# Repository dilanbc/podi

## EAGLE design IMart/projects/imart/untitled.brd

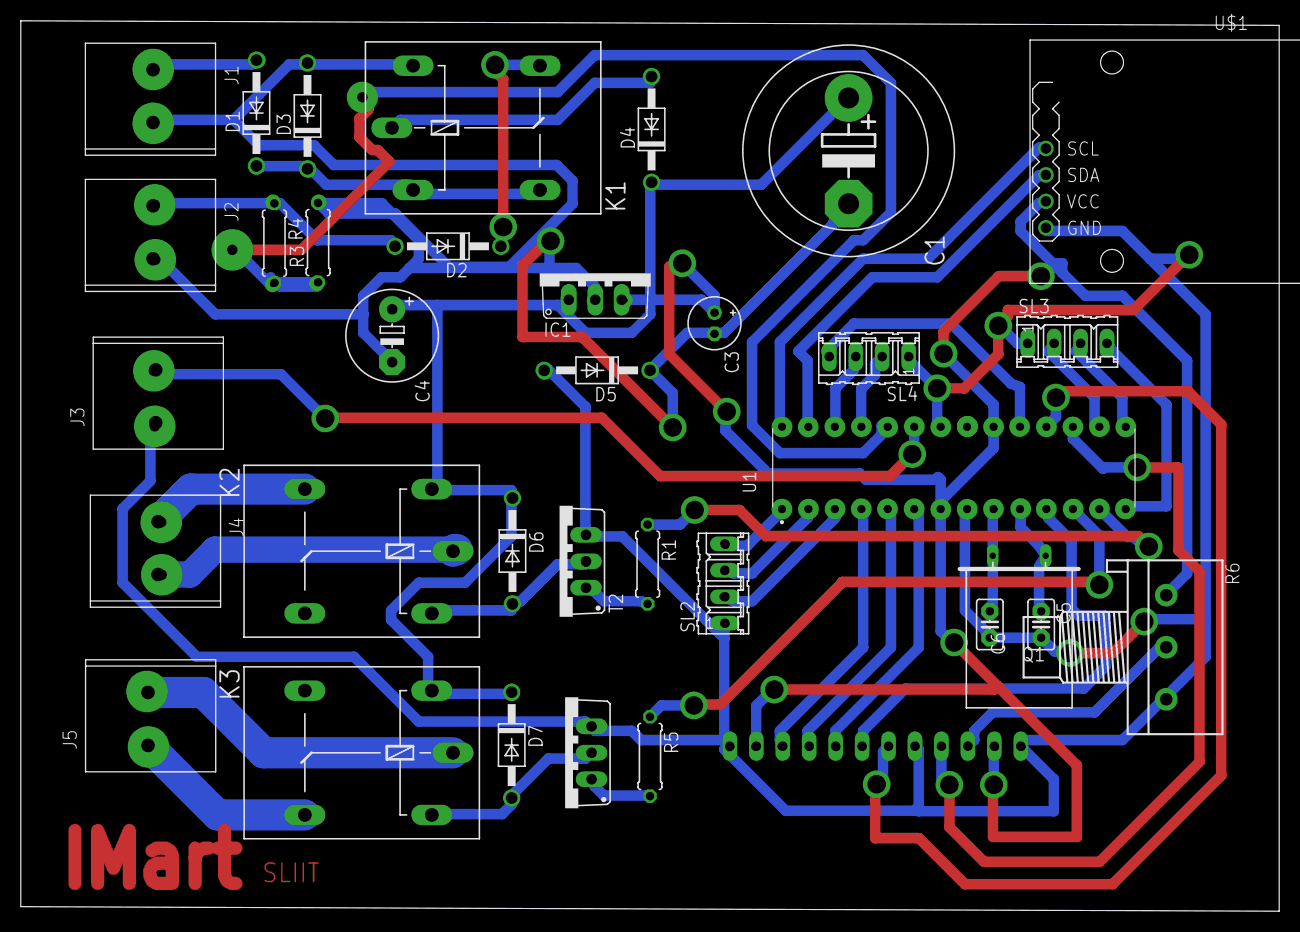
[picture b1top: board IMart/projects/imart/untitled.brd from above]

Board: 2 copper layers, 120.9 x 85.5 mm, 35 parts (1 on the bottom side), 41 nets.

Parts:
C1: EB20D
C3: E2-5
C4: E5-8,5
C5, C6: C025-025X050
D1, D2, D3, D4, D5, D6, D7: 1N4004; DO41-10
IC1: 788TV; TO220V
J1, J2, J3, J4, J5: 691201520002
K1, K2, K3: G5L; G5LE
Q1: Q
R1, R3, R4, R5: 0207/7
R6: 3RP/1610N
SL1: 12P
SL2, SL3, SL4: 04P
T1, T2: 2SC1306; TO220BV
U1: ATMEGA328P-PU; DIP-28
U$1: RTC-DS3231-AT24C32

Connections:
unnamed: D1.A, J1.1
unnamed: D2.A, J2.1, R4.1
unnamed: C1.-, C3.-, C4.-, D3.A, D5.C, IC1.2, J1.2, J2.2, K1.2, R3.2
unnamed: D2.C, K1.O
unnamed: D1.C, D3.C, K1.1, K1.S
unnamed: D4.A, K1.P
unnamed: R5.1, U1.12
unnamed: C3.+, IC1.3, R6.1, SL1.2, SL1.11, U1.7, U1.20, U$1.J1.5
unnamed: C5.2, C6.2, D5.A, J3.1, R6.3, SL1.1, SL1.5, SL1.12, SL2.1, SL3.1, SL4.1, T1.3, T2.3, U1.8, U1.22, U$1.J1.6
unnamed: C6.1, Q1.2, U1.9
unnamed: C5.1, Q1.1, U1.10
unnamed: U1.28, U$1.J1.3
unnamed: U1.27, U$1.J1.4
unnamed: SL1.7, U1.11
unnamed: R6.2, SL1.3
unnamed: SL1.4, U1.17
unnamed: SL1.6, U1.18
unnamed: SL1.8, U1.6
unnamed: SL1.9, U1.5
unnamed: SL1.10, U1.4
unnamed: J3.2, U1.23
unnamed: J4.2, K2.P
unnamed: J4.1, K2.S
unnamed: R3.1, R4.2, U1.24
unnamed: R1.1, U1.13
unnamed: R1.2, T2.1
unnamed: J5.2, K3.P
unnamed: D6.A, K2.2, T2.2
unnamed: J5.1, K3.O
unnamed: C1.+, C4.+, D4.C, D6.C, D7.C, IC1.1, K2.1, K3.1
unnamed: R5.2, T1.1
unnamed: D7.A, K3.2, T1.2
unnamed: SL2.4, U1.1
unnamed: SL2.3, U1.2
unnamed: SL2.2, U1.3
unnamed: SL3.4, U1.14
unnamed: SL3.3, U1.15
unnamed: SL3.2, U1.16
unnamed: SL4.2, U1.25
unnamed: SL4.3, U1.26
unnamed: SL4.4, U1.19

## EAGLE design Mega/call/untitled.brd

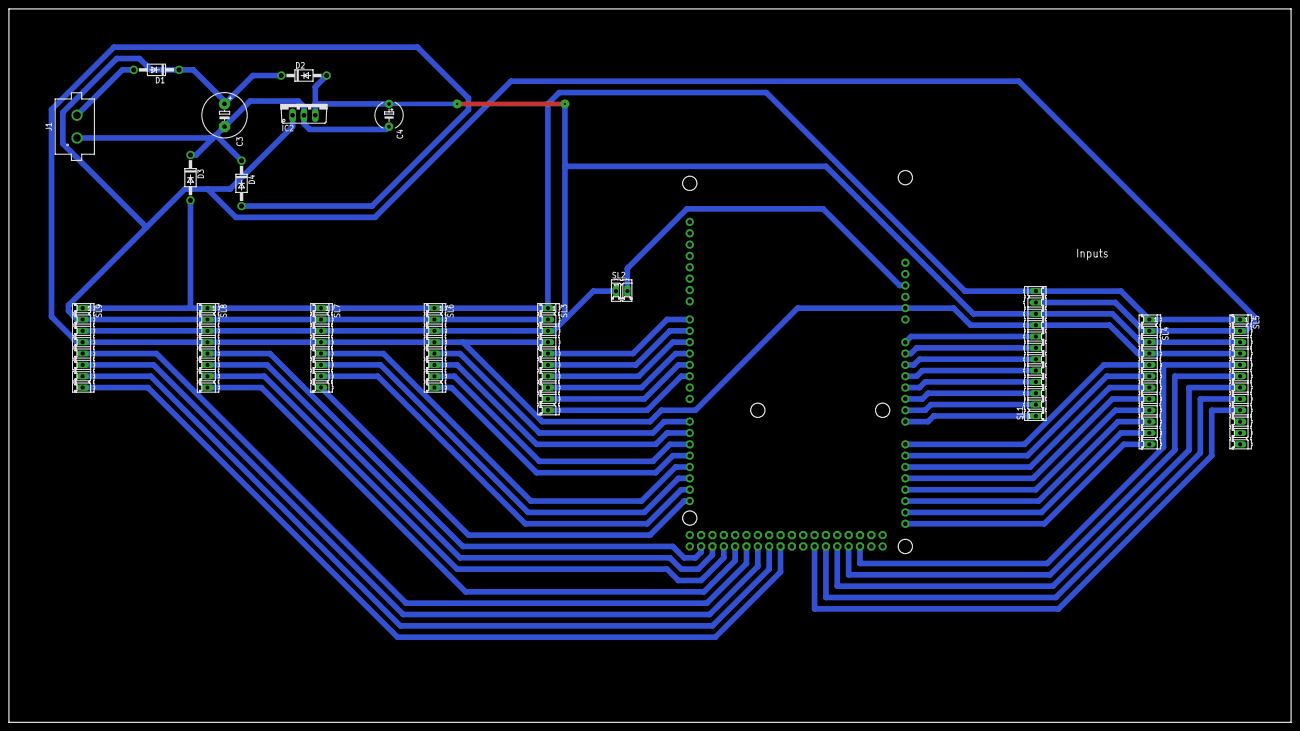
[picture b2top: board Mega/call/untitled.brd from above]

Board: 2 copper layers, 287.0 x 159.7 mm, 18 parts (1 on the bottom side), 50 nets.

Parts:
B1: ARDUINO_MEGA_R3FULL; ARDUINO_MEGA
C3: E5-10,5
C4: E5-6
D1, D2, D3, D4: 1N4004; DO41-10
IC2: 786TV; TO220V
J1: 691305530002
SL1, SL4, SL5: 12P
SL2: 02P
SL3: 10P
SL6, SL7, SL8, SL9: 08P

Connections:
GND: B1.GND@1, D4.A, SL1.9, SL3.4, SL4.4, SL5.4, SL6.4, SL7.4, SL8.4, SL9.4
unnamed: B1.A7, SL1.1
unnamed: B1.A6, SL1.2
unnamed: B1.A5, SL1.3
unnamed: B1.A4, SL1.4
unnamed: B1.A3, SL1.5
unnamed: B1.A2, SL1.6
unnamed: B1.A1, SL1.7
unnamed: B1.A0, SL1.8
unnamed: D3.A, SL1.12, SL3.1, SL4.1, SL5.1, SL6.1, SL7.1, SL8.1, SL9.1
unnamed: D1.A, J1.2
unnamed: C3.+, D1.C, D2.C, IC2.1, SL1.11, SL3.2, SL4.2, SL5.2, SL6.2, SL7.2, SL8.2, SL9.2
unnamed: C4.+, D2.A, IC2.3, SL1.10, SL2.1, SL3.3, SL4.3, SL5.3, SL6.3, SL7.3, SL8.3, SL9.3
unnamed: B1.2, SL3.10
unnamed: C3.-, C4.-, D3.C, D4.C, IC2.2, J1.1
unnamed: B1.3, SL3.9
unnamed: B1.5V@0, SL2.2
unnamed: B1.4, SL3.8
unnamed: B1.5, SL3.7
unnamed: B1.6, SL3.6
unnamed: B1.7, SL3.5
unnamed: B1.A8, SL4.5
unnamed: B1.A9, SL4.6
unnamed: B1.A10, SL4.7
unnamed: B1.A11, SL4.8
unnamed: B1.A12, SL4.9
unnamed: B1.A13, SL4.10
unnamed: B1.A14, SL4.11
unnamed: B1.A15, SL4.12
unnamed: B1.18, SL7.5
unnamed: B1.14, SL6.5
unnamed: B1.51, SL5.5
unnamed: B1.49, SL5.6
unnamed: B1.47, SL5.7
unnamed: B1.45, SL5.8
unnamed: B1.43, SL5.9
unnamed: B1.21, SL7.8
unnamed: B1.15, SL6.6
unnamed: B1.17, SL6.8
unnamed: B1.20, SL7.7
unnamed: B1.19, SL7.6
unnamed: B1.31, SL9.5
unnamed: B1.33, SL9.6
unnamed: B1.35, SL9.7
unnamed: B1.37, SL9.8
unnamed: B1.23, SL8.5
unnamed: B1.25, SL8.6
unnamed: B1.29, SL8.8
unnamed: B1.27, SL8.7
unnamed: B1.16, SL6.7

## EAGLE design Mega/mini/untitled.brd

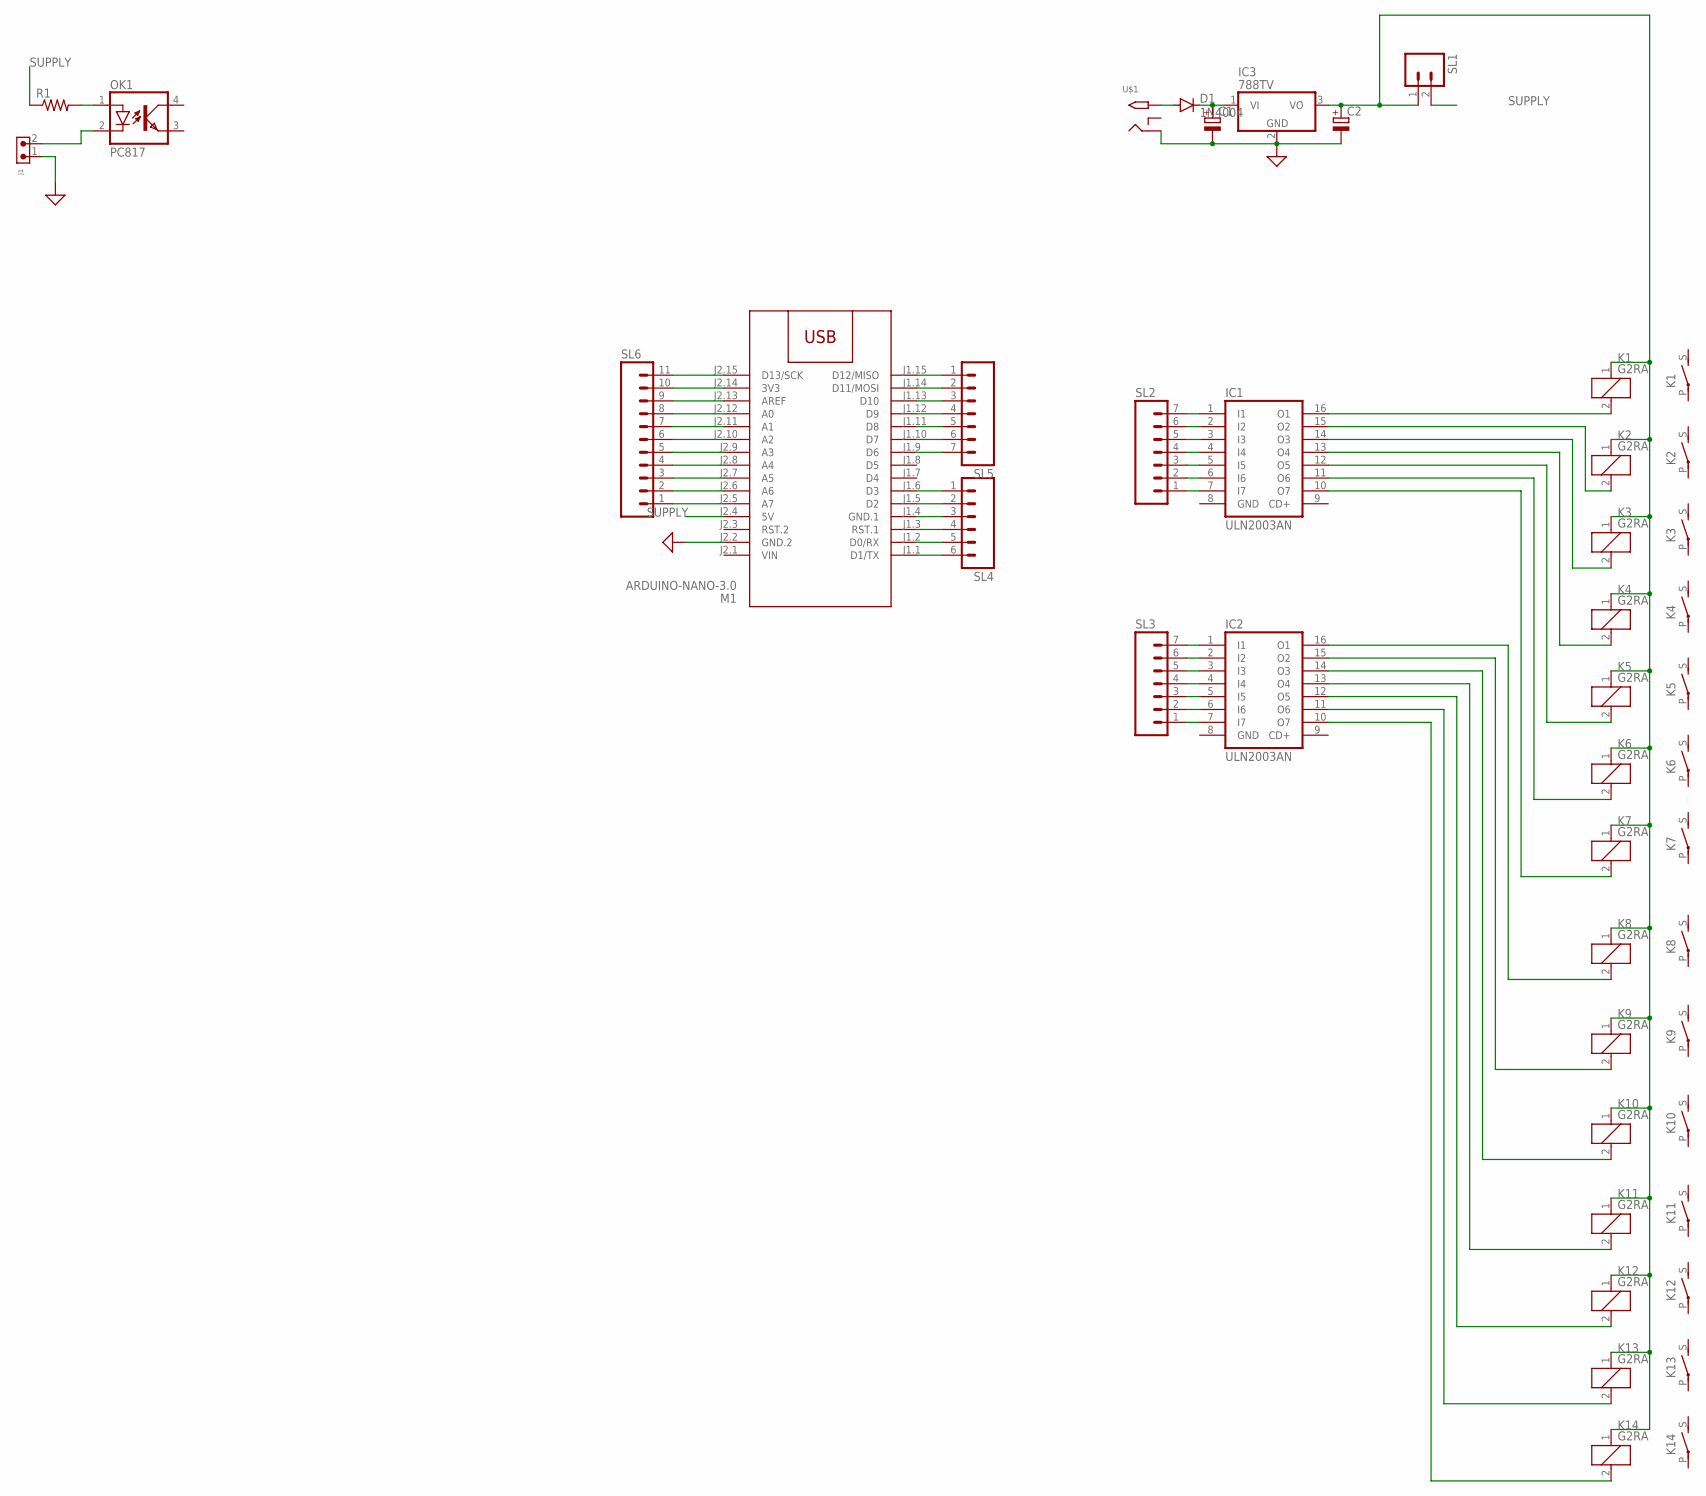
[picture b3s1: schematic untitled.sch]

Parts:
C1, C2: CPOL-EUE2.5-6; E2,5-6
D1: 1N4004; DO41-10
IC1, IC2: ULN2003AN; DIL16
IC3: 788TV; TO220V
J1: 691305530002
K1, K2, K3, K4, K5, K6, K7, K8, K9, K10, K11, K12, K13, K14: G2RA
M1: ARDUINO-NANO-3.0
OK1: PC817; DIL04
R1: R-US_0207/7; 0207/7
SL1: M02; 02P
SL2, SL3, SL5: M07; 07P
SL4: M06; 06P
SL6: M11; 11P
U$1: 2.1MMJACKTHM; PJ-102A

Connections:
GND: C1.-, C2.-, IC1.8 (GND), IC2.8 (GND), IC3.2 (GND), J1.1, M1.J2.2 (GND.2), U$1.RING
unnamed: IC1.16 (O1), K1.2
unnamed: IC1.15 (O2), K2.2
unnamed: IC1.14 (O3), K3.2
unnamed: IC1.13 (O4), K4.2
unnamed: IC1.12 (O5), K5.2
unnamed: IC1.11 (O6), K6.2
unnamed: IC1.10 (O7), K7.2
unnamed: IC2.16 (O1), K8.2
unnamed: IC2.15 (O2), K9.2
unnamed: IC2.14 (O3), K10.2
unnamed: IC2.13 (O4), K11.2
unnamed: IC2.12 (O5), K12.2
unnamed: IC2.11 (O6), K13.2
unnamed: IC2.10 (O7), K14.2
unnamed: D1.A, U$1.TIP
unnamed: C1.+, D1.C, IC3.1 (VI)
unnamed: IC1.7 (I7), SL2.1
unnamed: C2.+, IC3.3 (VO), K1.1, K2.1, K3.1, K4.1, K5.1, K6.1, K7.1, K8.1, K9.1, K10.1, K11.1, K12.1, K13.1, K14.1, SL1.1
unnamed: IC1.6 (I6), SL2.2
unnamed: IC1.5 (I5), SL2.3
unnamed: IC1.4 (I4), SL2.4
unnamed: IC1.3 (I3), SL2.5
unnamed: IC1.2 (I2), SL2.6
unnamed: IC1.1 (I1), SL2.7
unnamed: IC2.7 (I7), SL3.1
unnamed: IC2.6 (I6), SL3.2
unnamed: IC2.5 (I5), SL3.3
unnamed: IC2.4 (I4), SL3.4
unnamed: IC2.3 (I3), SL3.5
unnamed: IC2.2 (I2), SL3.6
unnamed: IC2.1 (I1), SL3.7
unnamed: M1.J1.6 (D3), SL4.1
unnamed: M1.J1.5 (D2), SL4.2
unnamed: M1.J1.4 (GND.1), SL4.3
unnamed: M1.J1.3 (RST.1), SL4.4
unnamed: M1.J1.2 (D0/RX), SL4.5
unnamed: M1.J1.1 (D1/TX), SL4.6
unnamed: M1.J1.15 (D12/MISO), SL5.1
unnamed: M1.J1.14 (D11/MOSI), SL5.2
unnamed: M1.J1.13 (D10), SL5.3
unnamed: M1.J1.12 (D9), SL5.4
unnamed: M1.J1.11 (D8), SL5.5
unnamed: M1.J1.10 (D7), SL5.6
unnamed: M1.J1.9 (D6), SL5.7
unnamed: M1.J2.5 (A7), SL6.1
unnamed: M1.J2.6 (A6), SL6.2
unnamed: M1.J2.7 (A5), SL6.3
unnamed: M1.J2.8 (A4), SL6.4
unnamed: M1.J2.9 (A3), SL6.5
unnamed: M1.J2.10 (A2), SL6.6
unnamed: M1.J2.11 (A1), SL6.7
unnamed: M1.J2.12 (A0), SL6.8
unnamed: M1.J2.13 (AREF), SL6.9
unnamed: M1.J2.14 (3V3), SL6.10
unnamed: M1.J2.15 (D13/SCK), SL6.11
unnamed: J1.2, OK1.2 (C)
unnamed: OK1.1 (A), R1.2
SUPPLY: M1.J2.4 (5V), R1.1, SL1.2
VIN: M1.J2.1 (VIN)

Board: 2 copper layers, 31 parts (0 on the bottom side), 59 nets, no tracks yet.

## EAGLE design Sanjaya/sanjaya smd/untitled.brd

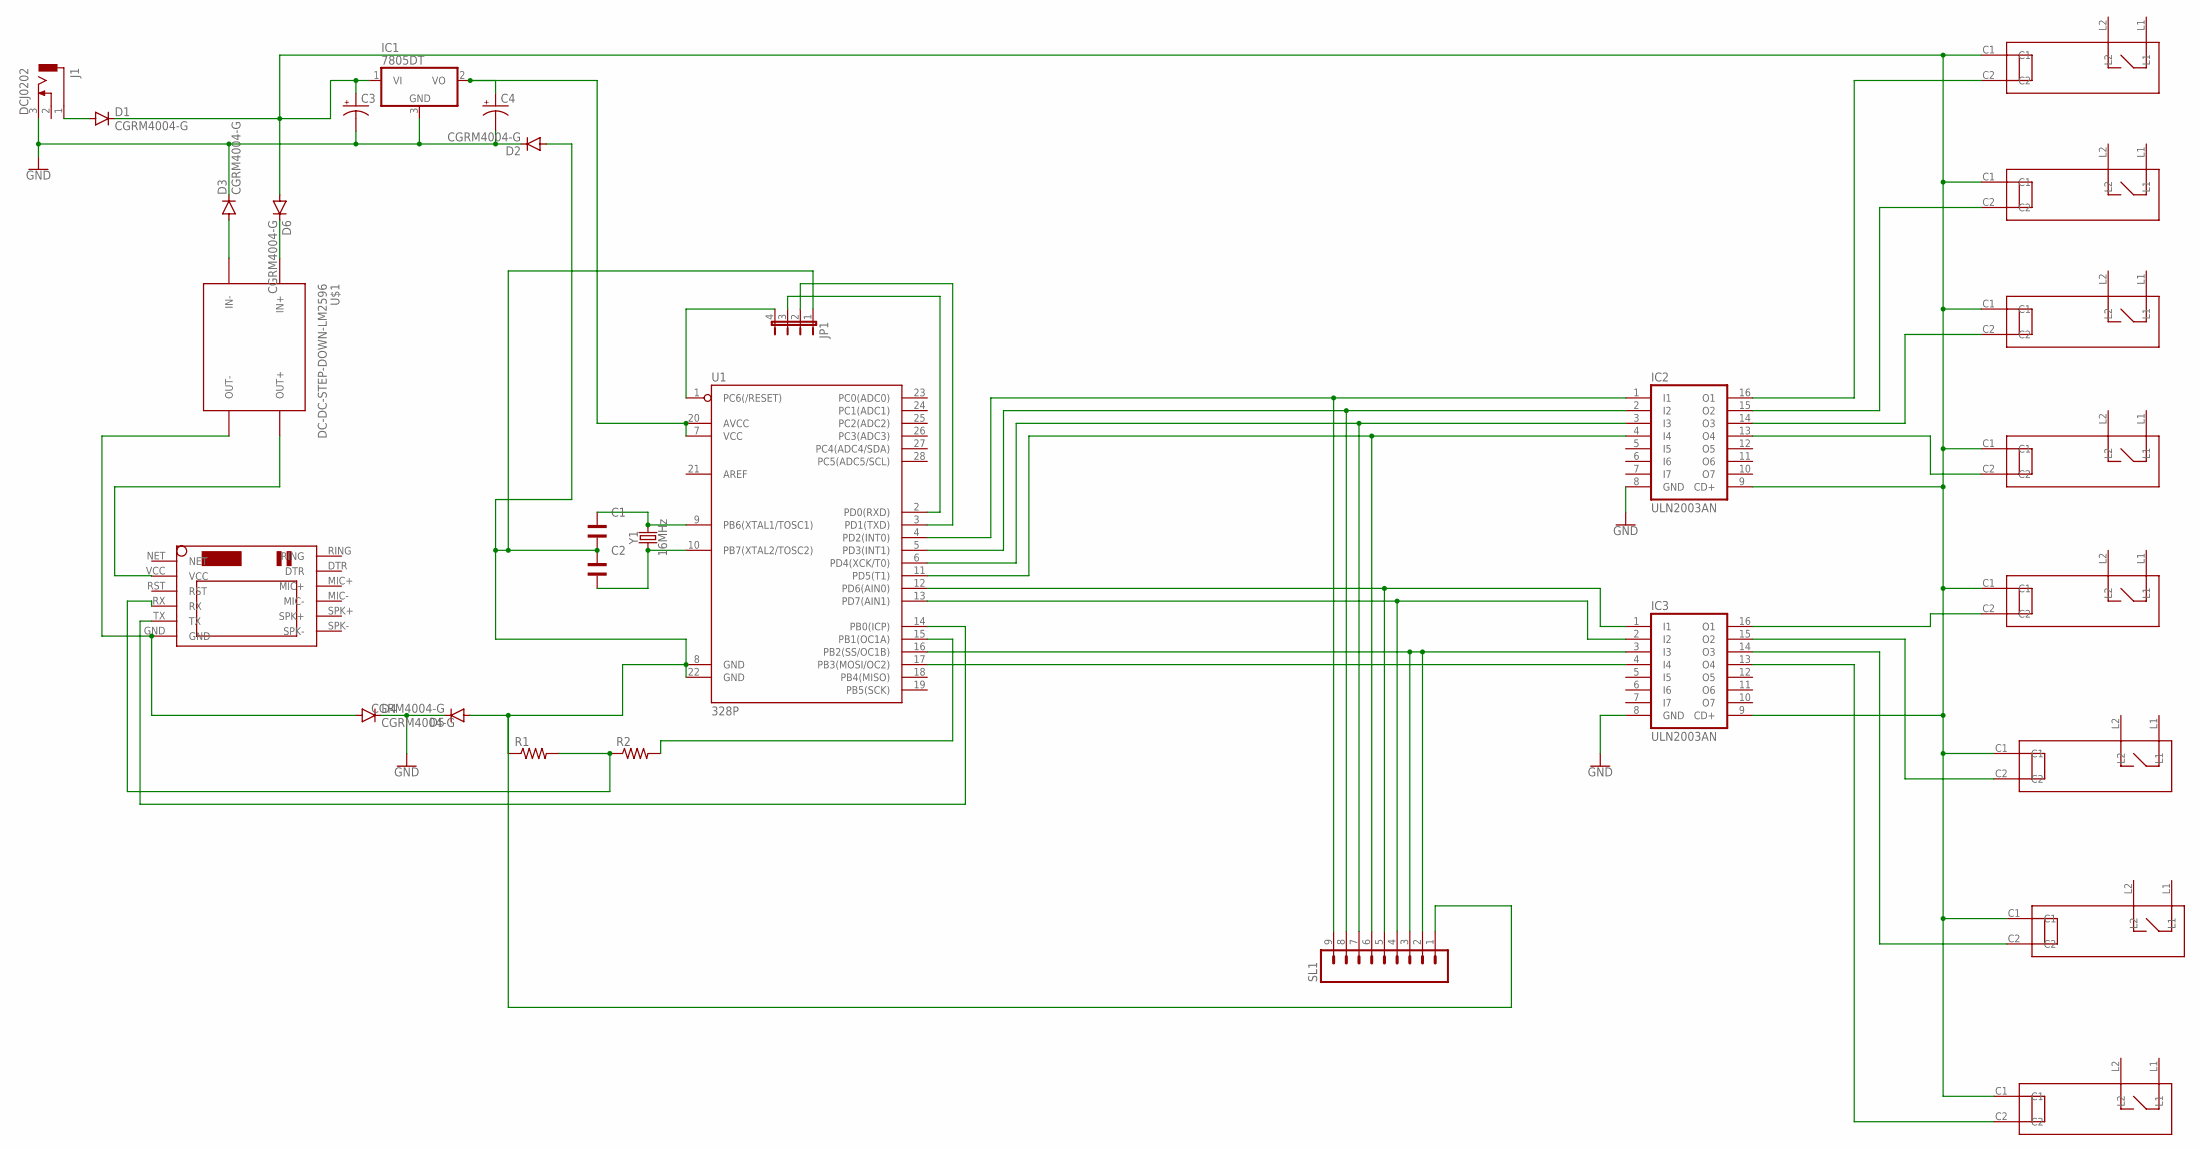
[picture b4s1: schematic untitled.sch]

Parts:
C1, C2: WCAP-CSGP_1206_885012008001; WCAP-CSGP_1206
C3: CPOL-USE3.5-8; E3,5-8
C4: CPOL-USE2.5-5; E2,5-5
D1, D2, D3, D4, D5, D6: CGRM4004-G; SOD-123_MINI-SMA
IC1: 7805DT; TO252
IC2, IC3: ULN2003AN; DIL16
J1: DCJ0202
JP1: JP4E; JP4
R1, R2: R-US_R1206; R1206
SL1: M09; 09P
U1: 328P; DIP28
U$1: DC-DC-STEP-DOWN-LM2596
U$2: SIM800LMODULE
U$3, U$4, U$5, U$6, U$7, U$8, U$9, U$10: HF46F
Y1: 16MHz; HC49US

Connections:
GND: C3.-, C4.-, D2.C, D3.C, D4.C, D5.C, IC1.3 (GND), IC2.8 (GND), IC3.8 (GND), J1.3
unnamed: IC2.1 (I1), SL1.9, U1.4 (PD2(INT0))
unnamed: C1.2, U1.9 (PB6(XTAL1/TOSC1)), Y1.2
unnamed: C2.1, U1.10 (PB7(XTAL2/TOSC2)), Y1.1
unnamed: C3.+, D1.C, D6.A, IC1.1 (VI), IC2.9 (CD+), IC3.9 (CD+), U$3.C1, U$4.C1, U$5.C1, U$6.C1, U$7.C1, U$8.C1, U$9.C1, U$10.C1
unnamed: C4.+, IC1.2 (VO), U1.7 (VCC), U1.20 (AVCC)
unnamed: D1.A, J1.1
unnamed: D3.A, U$1.IN-
unnamed: U1.14 (PB0(ICP)), U$2.TX
unnamed: U$1.OUT+, U$2.VCC
unnamed: C1.1, C2.2, D2.A, D5.A, JP1.1, R1.1, SL1.1, U1.8 (GND), U1.22 (GND)
unnamed: D4.A, U$1.OUT-, U$2.GND
unnamed: R1.2, R2.1, U$2.RX
unnamed: R2.2, U1.15 (PB1(OC1A))
unnamed: IC2.2 (I2), SL1.8, U1.5 (PD3(INT1))
unnamed: IC2.3 (I3), SL1.7, U1.6 (PD4(XCK/T0))
unnamed: IC2.4 (I4), SL1.6, U1.11 (PD5(T1))
unnamed: IC3.1 (I1), SL1.5, U1.12 (PD6(AIN0))
unnamed: IC3.2 (I2), SL1.4, U1.13 (PD7(AIN1))
unnamed: IC3.3 (I3), SL1.2, SL1.3, U1.16 (PB2(SS/OC1B))
unnamed: IC3.4 (I4), U1.17 (PB3(MOSI/OC2))
unnamed: IC2.16 (O1), U$3.C2
unnamed: IC2.15 (O2), U$4.C2
unnamed: IC2.14 (O3), U$5.C2
unnamed: IC2.13 (O4), U$6.C2
unnamed: IC3.16 (O1), U$7.C2
unnamed: IC3.15 (O2), U$8.C2
unnamed: IC3.14 (O3), U$9.C2
unnamed: IC3.13 (O4), U$10.C2
unnamed: D6.C, U$1.IN+
unnamed: JP1.4, U1.1 (PC6(/RESET))
unnamed: JP1.3, U1.2 (PD0(RXD))
unnamed: JP1.2, U1.3 (PD1(TXD))

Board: 2 copper layers, 30 parts (0 on the bottom side), 33 nets, no tracks yet.

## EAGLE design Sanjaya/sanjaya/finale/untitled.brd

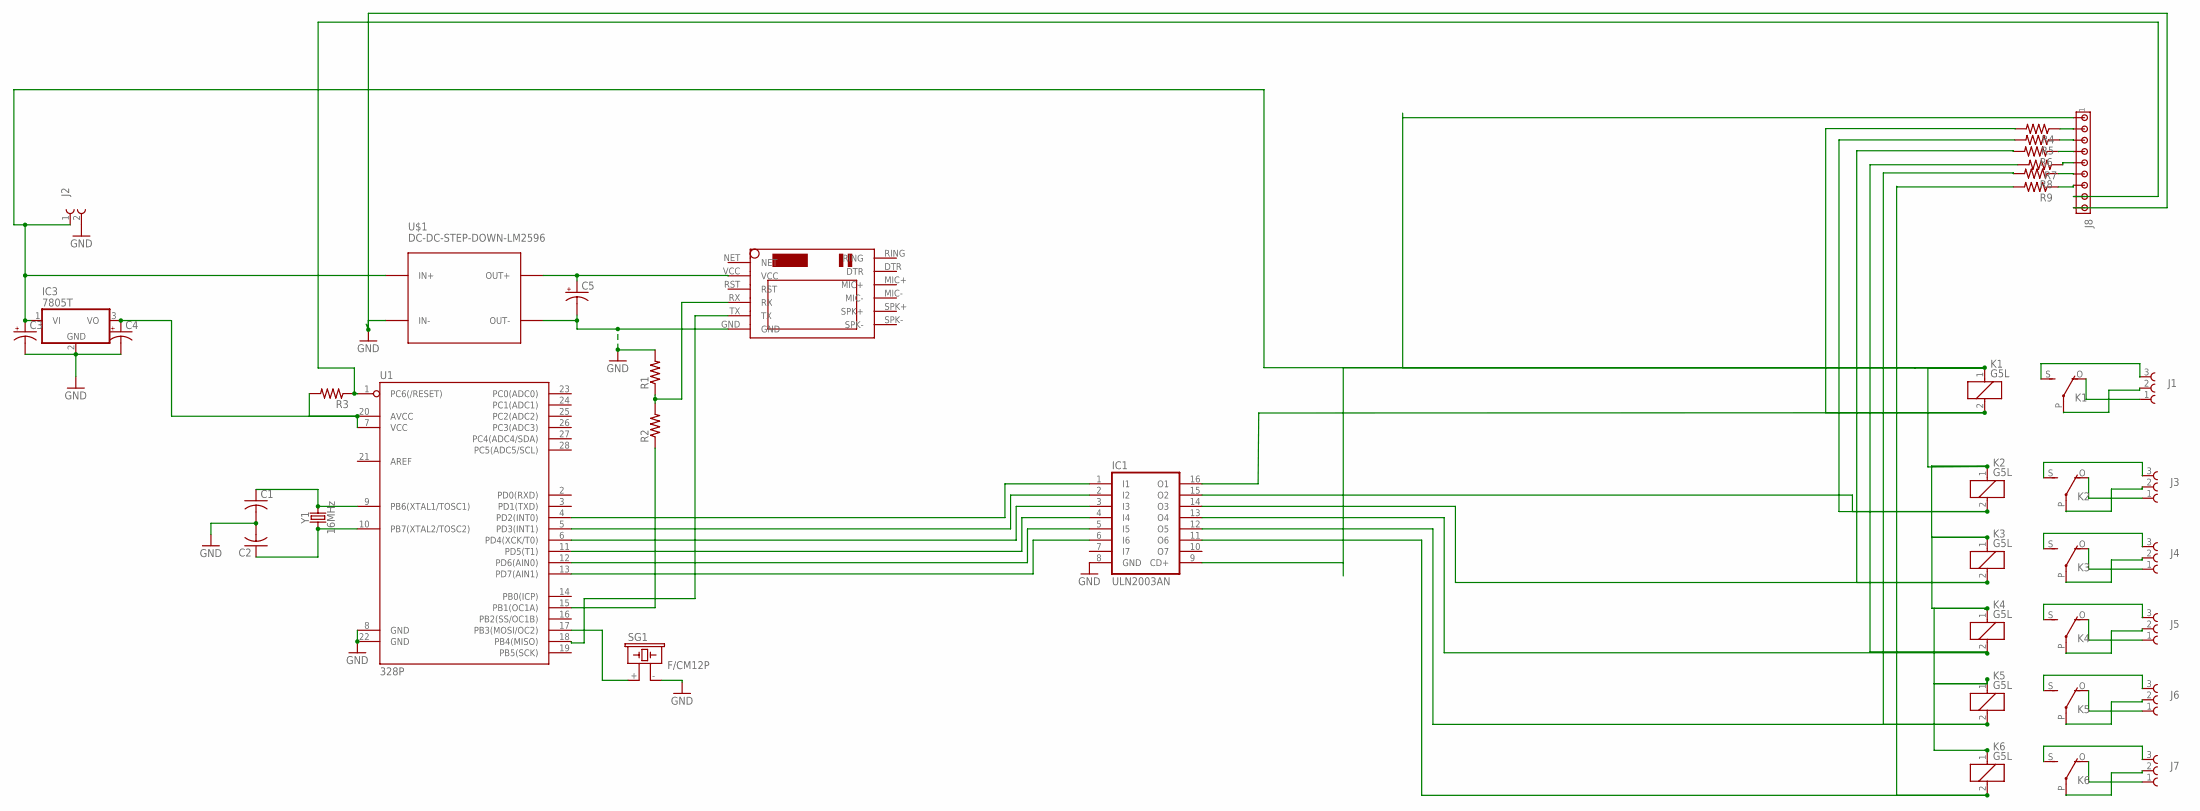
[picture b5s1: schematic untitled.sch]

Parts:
C1, C2: C-US025-024X044; C025-024X044
C3, C4: CPOL-USE2.5-5; E2,5-5
C5: CAPACITOR-PE5-8.5; E5-8,5
IC1: ULN2003AN; DIL16
IC3: 7805T; TO220H
J1, J3, J4, J5, J6, J7: 691216700003
J2: 691217910002
J8: MTA09-100; 10X09MTA
K1, K2, K3, K4, K5, K6: G5L; G5LE
R1, R2, R3, R4, R5, R6, R7, R8, R9: R-US_0204/7; 0204/7
SG1: F/CM12P
U1: 328P; DIP28
U$1: DC-DC-STEP-DOWN-LM2596
U$2: SIM800LMODULE
Y1: 16MHz; HC49US

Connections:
GND: C1.2, C2.2, C3.-, C4.-, C5.-, IC1.8 (GND), IC3.2 (GND), J2.2, J8.9, R1.2, SG1.- (2), U1.8 (GND), U1.22 (GND), U$1.IN-, U$1.OUT-, U$2.GND
unnamed: IC1.1 (I1), U1.4 (PD2(INT0))
unnamed: C2.1, U1.10 (PB7(XTAL2/TOSC2)), Y1.1
unnamed: C1.1, U1.9 (PB6(XTAL1/TOSC1)), Y1.2
unnamed: IC1.2 (I2), U1.5 (PD3(INT1))
unnamed: IC1.3 (I3), U1.6 (PD4(XCK/T0))
unnamed: IC1.4 (I4), U1.11 (PD5(T1))
unnamed: IC1.5 (I5), U1.12 (PD6(AIN0))
unnamed: IC1.6 (I6), U1.13 (PD7(AIN1))
unnamed: IC1.15 (O2), K2.2, R5.2
unnamed: C4.+, IC3.3 (VO), R3.2, U1.7 (VCC), U1.20 (AVCC)
unnamed: J8.2, R4.1
unnamed: IC1.14 (O3), K3.2, R6.2
unnamed: IC1.13 (O4), K4.2, R7.2
unnamed: C5.+, U$1.OUT+, U$2.VCC
unnamed: U1.18 (PB4(MISO)), U$2.TX
unnamed: R2.1, U1.15 (PB1(OC1A))
unnamed: R1.1, R2.2, U$2.RX
unnamed: IC1.12 (O5), K5.2, R8.2
unnamed: J1.2, K1.P
unnamed: J1.3 (1), K1.S
unnamed: J1.1 (3), K1.O
unnamed: J8.3, R5.1
unnamed: IC1.16 (O1), K1.2, R4.2
unnamed: J3.2, K2.P
unnamed: J3.3 (1), K2.S
unnamed: J3.1 (3), K2.O
unnamed: J8.8, R3.1, U1.1 (PC6(/RESET))
unnamed: J4.2, K3.P
unnamed: J4.3 (1), K3.S
unnamed: J4.1 (3), K3.O
unnamed: SG1.+ (1), U1.17 (PB3(MOSI/OC2))
unnamed: J5.2, K4.P
unnamed: J5.3 (1), K4.S
unnamed: J5.1 (3), K4.O
unnamed: J8.4, R6.1
unnamed: J6.2, K5.P
unnamed: J6.3 (1), K5.S
unnamed: J6.1 (3), K5.O
unnamed: C3.+, IC1.9 (CD+), IC3.1 (VI), J2.1, J8.1, K1.1, K2.1, K3.1, K4.1, K5.1, K6.1, U$1.IN+
unnamed: J7.2, K6.P
unnamed: J7.3 (1), K6.S
unnamed: J7.1 (3), K6.O
unnamed: J8.5, R7.1
unnamed: J8.6, R8.1
unnamed: J8.7, R9.1
unnamed: IC1.11 (O6), K6.2, R9.2

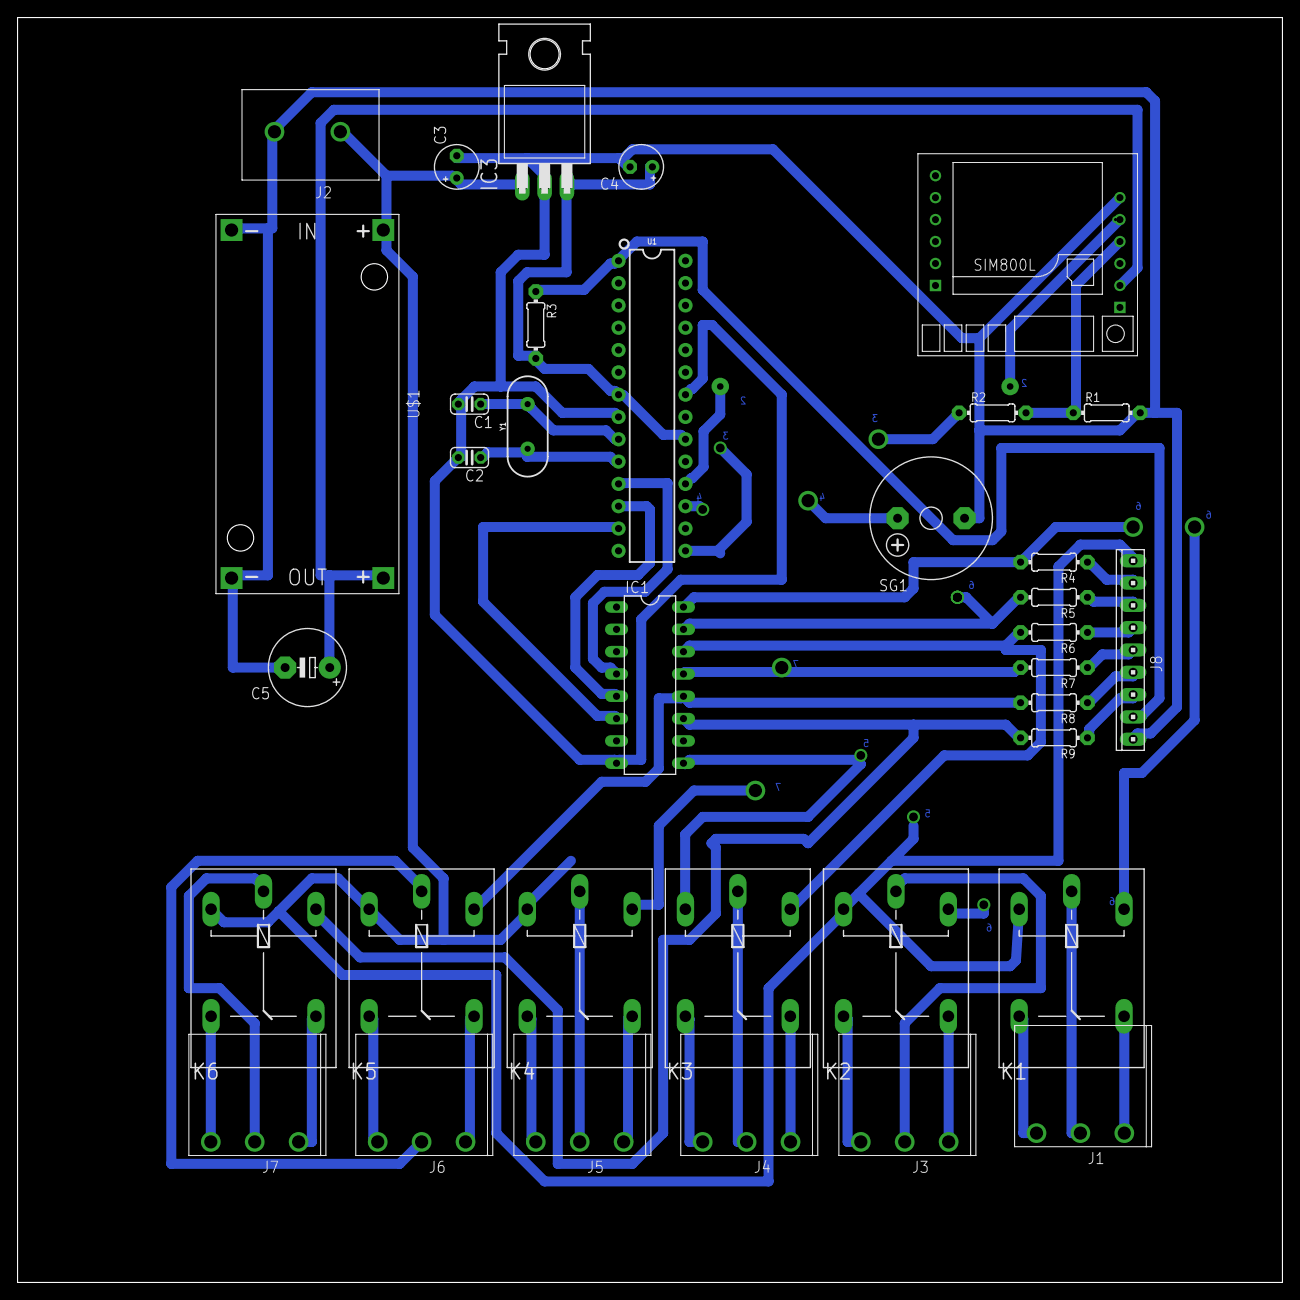
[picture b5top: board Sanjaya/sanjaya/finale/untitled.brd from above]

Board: 2 copper layers, 144.0 x 144.0 mm, 35 parts (0 on the bottom side), 47 nets.

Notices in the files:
parts and their libraries:
diy-modules: Released under the Creative Commons Attribution 4.0 International License: http://creativecommons.org/licenses/by/4.0
Wurth_Isolated Converter_MagI³C-FISM: Copyright: Würth Elektronik
